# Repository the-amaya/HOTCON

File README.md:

# HOTCON

HOTtub CONtrol system

This project is the hardware and software for my hottub. Current features include hardware control, automated tub
control logic including heating control and filter cycles.

NOTICE: use this at your own risk. if you break your hot tub or set it on fire or anything else I am not responsible. I
have taken steps to ensure this software is fail-safe but controlling a heater purely in software is inherently
dangerous.

# Usage

`python main.py`

Currently I have not implemented buttons or a display on the tub for control. This software provides a web app and API
for tub control.

The main web interface is available at 127.0.0.1:8000
the admin control panel is at 127.0.0.1:8000/admin
and API documentation is available at 127.0.0.1:8000/docs

In tub_control.py you need to set the ID for the temperature sensors on lines 432-437.
In index.html and admin.html you need to set the IP or URL for your hottub. (lines 138-139 for index.html and 236-237
for admin.html)

# Hardware

need to document the hardware and put together a BOM.

The heart of the project is a raspberry pi 4. using a number of support components I built a custom control board to
interface with the tub hardware. The heater and main pumps use 2-pole contactors and everything else uses single pole
relays.

Currently implemented hardware features:

- Main jet pumps
- circulator pump
- heater
- light
- fan
- blower
- ozone generator

Still to come hardware features:

- upper controls for the tub (buttons and a 7-segment display is planned)

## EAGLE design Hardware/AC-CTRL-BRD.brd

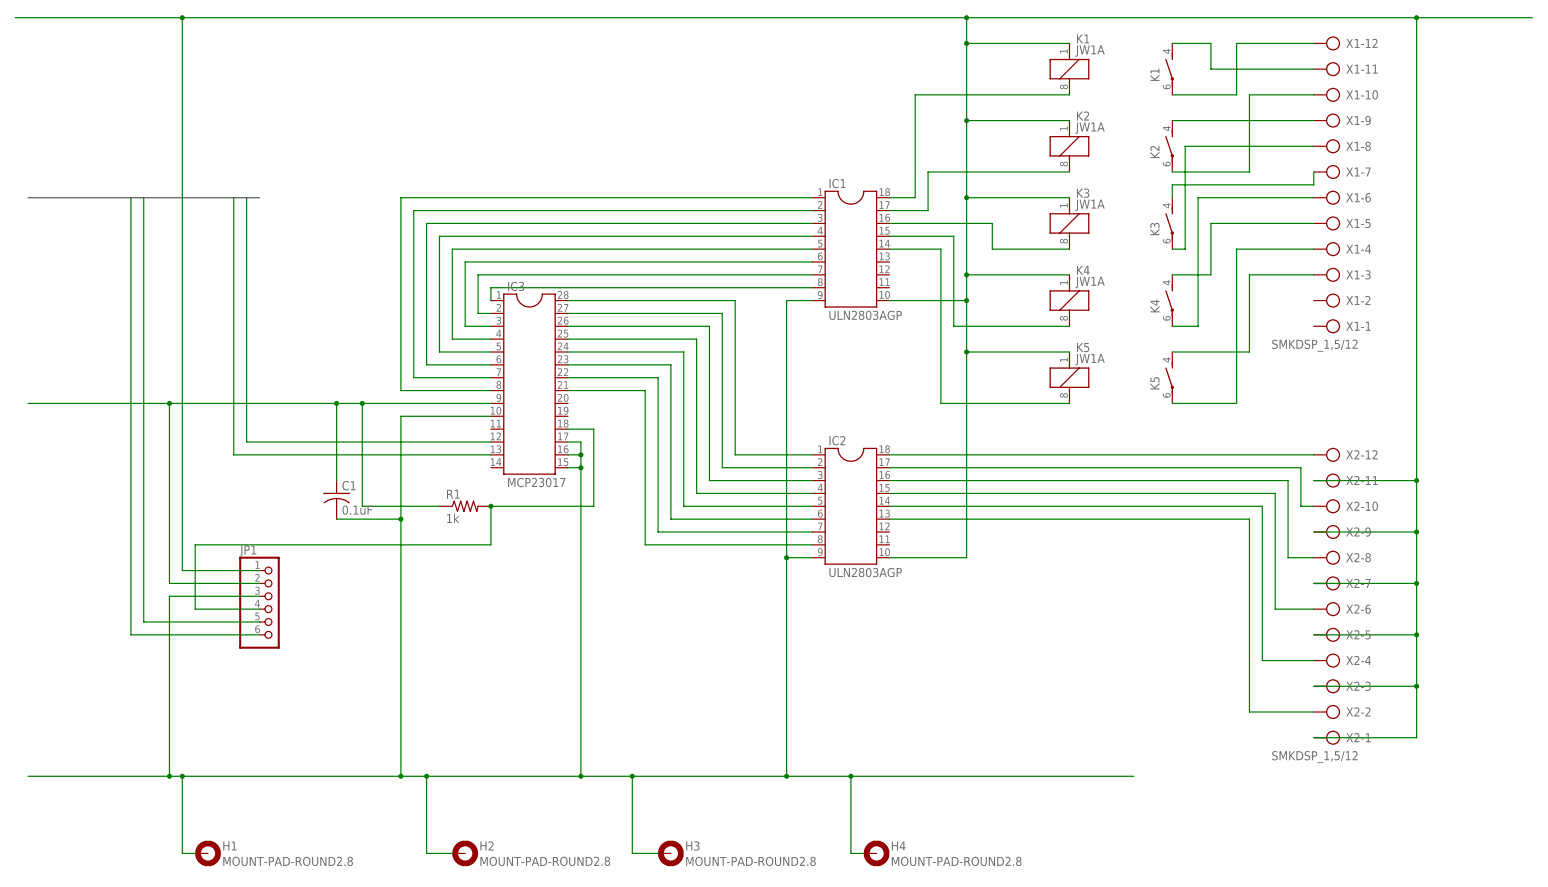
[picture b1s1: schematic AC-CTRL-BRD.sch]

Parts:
C1: 0.1uF; C050-024X044
H1, H2, H3, H4: MOUNT-PAD-ROUND2.8; 2,8-PAD
IC1, IC2: ULN2803AGP; DIL18
IC3: MCP23017; DIL28-3
JP1: PINHD-1X6; 1X06
K1, K2, K3, K4, K5: JW1A
R1: 1k; 0204/7
X1, X2: SMKDSP_1,5/12

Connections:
5V: C1.1, IC3.9, JP1.2, R1.1
12V: IC1.10, IC2.10, JP1.1, K1.1, K2.1, K3.1, K4.1, K5.1, X2.1, X2.3, X2.5, X2.7, X2.9, X2.11
GROUND: C1.2, H1.B2,8, H2.B2,8, H3.B2,8, H4.B2,8, IC1.9, IC2.9, IC3.10, IC3.15, IC3.16, IC3.17, JP1.3
unnamed: IC2.7, IC3.22
unnamed: IC1.18, K1.8 (2)
unnamed: IC1.17, K2.8 (2)
unnamed: IC1.16, K3.8 (2)
unnamed: IC1.15, K4.8 (2)
unnamed: IC1.14, K5.8 (2)
unnamed: IC2.8, IC3.21
unnamed: IC2.6, IC3.23
unnamed: IC2.5, IC3.24
unnamed: IC2.4, IC3.25
unnamed: IC2.3, IC3.26
unnamed: IC2.2, IC3.27
unnamed: IC2.1, IC3.28
unnamed: IC1.8, IC3.1
unnamed: IC1.7, IC3.2
unnamed: IC1.6, IC3.3
unnamed: IC1.5, IC3.4
unnamed: IC1.4, IC3.5
unnamed: IC1.3, IC3.6
unnamed: IC1.2, IC3.7
unnamed: IC1.1, IC3.8
unnamed: IC3.18, JP1.4, R1.2
unnamed: K1.4 (S), X1.11
unnamed: K1.6, X1.12
unnamed: K2.4 (S), X1.9
unnamed: K2.6, X1.10
unnamed: K3.4 (S), X1.7
unnamed: K3.6, X1.8
unnamed: K4.4 (S), X1.5
unnamed: K4.6, X1.6
unnamed: K5.6, X1.4
unnamed: K5.4 (S), X1.3
unnamed: IC2.18, X2.12
unnamed: IC2.17, X2.10
unnamed: IC2.16, X2.8
unnamed: IC2.15, X2.6
unnamed: IC2.14, X2.4
unnamed: IC2.13, X2.2
SCL: IC3.12, JP1.6
SDA: IC3.13, JP1.5

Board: 2 copper layers, 17 parts (0 on the bottom side), 43 nets, no tracks yet.

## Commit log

2021-10-04 Update README.md
    initial roadmap
2021-10-04 continued board work
2021-10-13 started work on main
    started working on main.py
2021-10-16 created tub control
    tub_control.py will be used to control all hardware outputs (primarily the AC-CTRL-BRD)
2024-11-23 the meaty commit
    huge commit of all the work I have done so far
2024-11-23 Update tub_control.py
    commented out a print line I was using for debugging
2024-11-23 Delete requirements.txt
    deleted outdated requirements. need to make a new one at some point
2024-11-28 better freeze protection
